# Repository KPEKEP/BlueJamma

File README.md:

# Arcade Bluetooth Controller Adapter "BlueJamma"

## Overview
This project provides a hardware and software solution to add Bluetooth gamepad support to Jamma/Chamma arcade boards (like Pandora Box), while maintaining the original physical controls functionality. The adapter allows connecting up to 2 Bluetooth gamepads simultaneously with the existing control panel.

The device is built around the ESP32-C3 SuperMini development board, which provides an excellent balance of size, features, and cost. The control program is based on the BluePad32 library and can be found in the `sketch` folder of this repository.

## Features
- Supports up to 2 Bluetooth gamepads simultaneously
- Maintains original control panel functionality
- Compatible with Jamma/Chamma arcade boards
- Easy installation and setup
- Open-source hardware and software

## Hardware
The project uses the ESP32-C3 SuperMini form factor for its compact size and built-in USB capabilities. A complete list of required components and materials can be found in the interactive [Bill of Materials](bom/ibom.html).

The PCB design incorporates elements from the [JammaKludge project](https://github.com/estechnical/jammakludge) by estechnical, which provided valuable reference for the Jamma connector implementation.

## PCB Design

## Enclosure Design
Check out the 3D render of the enclosure design:
https://github.com/KPEKEP/BlueJamma/raw/main/enclosure/export/rc3/rc3_v1.avi

STEP files for the enclosure are available in the [enclosure/export/rc3/](enclosure/export/rc3/) folder.

## Assembled Device

Assembled device: https://github.com/KPEKEP/BlueJamma/raw/main/images/assembled.MOV

Watch a demo of the device working with Bluetooth controllers:
https://github.com/KPEKEP/BlueJamma/raw/main/images/demo.mp4

## Risk Disclaimer
### ATTENTION: The device was tested only with Pandora Box, which is a Chamma board. Jamma boards are not tested yet.
### Chamma and Jamma compatibility
### IMPORTANT: The additional kicker harnesses are not supported yet.

BlueJamma was designed to be a pass-through between the arcade board and physical controls or whatever is connected next. When no input is coming from gamepads, regardless of their connection status, the system behaves as it would be a straight connection between the arcade board and physical controllers.
If an arcade board has Chamma (6-button), or regular Jamma (3-button) interface, it should work.
Please refer to the image of the layout below (side by side of top and bottom side of the PCB) and pay attention to the traces between 25,26,27,C,D,E on the right side of the PCB.

**USE AT YOUR OWN RISK**: The hardware and software in this project are provided "as is", without warranty of any kind, express or implied. The creators and contributors of this project accept no responsibility or liability for any damage, injury, or loss resulting from the use of this project's hardware, software, or documentation.

- We are not responsible for any damage to your arcade board, control panel, or other equipment
- Modify your hardware at your own risk
- Always verify connections and power requirements before use

### Components Attribution
This project uses:
- Open-source libraries and components, all properly credited in the source code
- Originally written code and hardware designs
- Third-party libraries used under their respective licenses (see Dependencies section)

### Non-Commercial Use License
This project is released under a Non-Commercial Use License. You are free to:
- Use this project for personal, non-commercial purposes
- Modify and adapt the code for personal use
- Share the project with others, provided you maintain the same license

You may NOT:
- Use this project for commercial purposes
- Sell products based on this project
- Include this project in commercial applications

## TODO
- [ ] Add kicker harness support
- [ ] Add a shadow-line for the top and bottom parts of the enclosure
- [ ] Test with Jamma board and different harness combinations
- [ ] Test video signal quality with\without BlueJamma. Some decoupling circuitry might be need.
      
## Authors and Acknowledgment
Pavel Nakaznenko, 2025

This project relies on and gratefully acknowledges the following tools and projects:

- [BluePad32](https://github.com/ricardoquesada/bluepad32) - The excellent Bluetooth gamepad support library that powers the controller functionality
- [ESP32-C3](https://www.espressif.com/en/products/socs/esp32-c3) - The RISC-V based microcontroller from Espressif
- [Arduino IDE](https://www.arduino.cc/en/software) - The development environment used for programming
- [KiCad](https://www.kicad.org/) - The open-source software used for electronic design
- [JLCPCB](https://jlcpcb.com/) - PCB manufacturing and assembly services
- [JammaKludge](https://github.com/estechnical/jammakludge) - Reference materials for Jamma connector implementation

Special thanks to all the open-source contributors and communities behind these projects.

---

Remember: This project is for non-commercial use only. All modifications and usage are at your own risk. 

LICENSE: [CC BY-NC-SA 4.0](https://creativecommons.org/licenses/by-nc-sa/4.0/)

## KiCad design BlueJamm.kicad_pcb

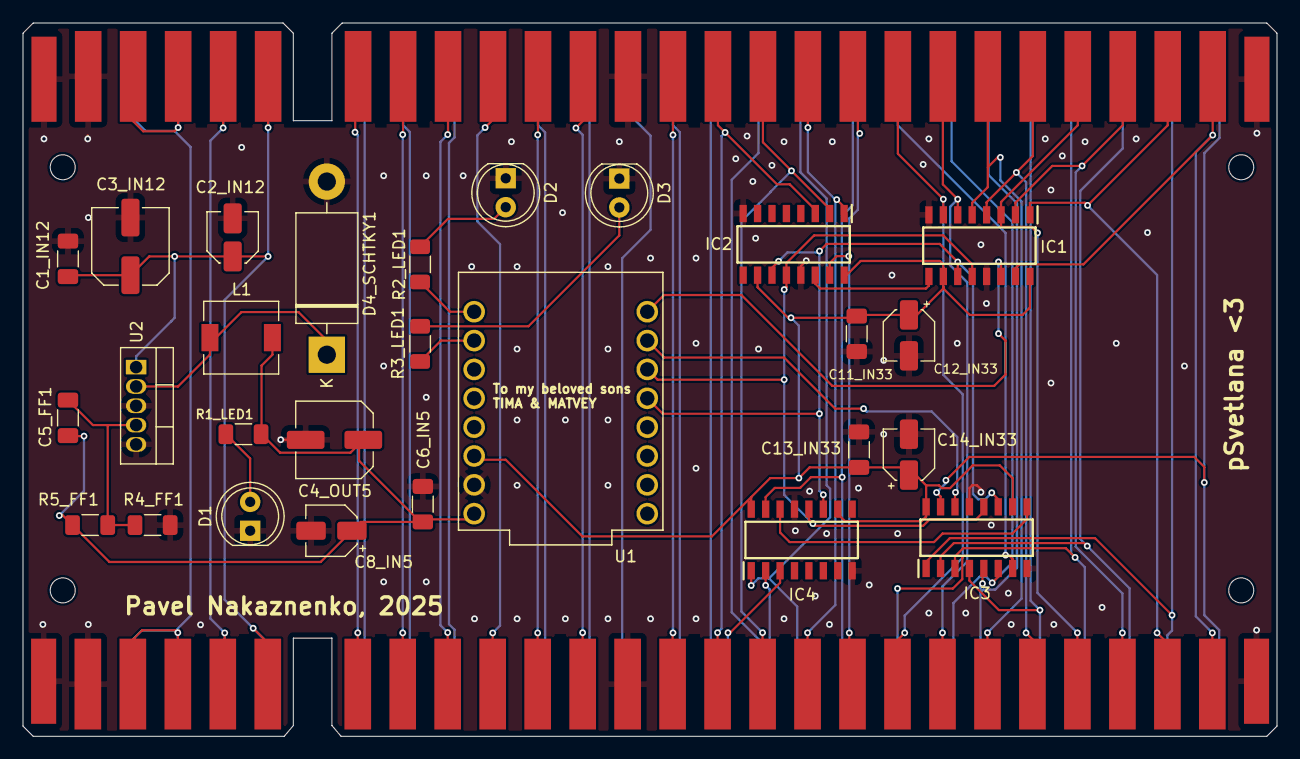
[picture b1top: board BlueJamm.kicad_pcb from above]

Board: 2 copper layers, 110.4 x 62.8 mm, 33 parts (0 on the bottom side), 57 nets.

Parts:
C1_IN12, C6_IN5, C11_IN33, C13_IN33: 0.1u; C_1206_3216Metric_Pad1.33x1.80mm_HandSolder
C2_IN12: 10u; C_Elec_4x5.4
C3_IN12: 100u; C_Elec_6.3x5.4
C4_OUT5: 220u; C_Elec_6.3x7.7
C5_FF1: 10n; C_1206_3216Metric_Pad1.33x1.80mm_HandSolder
C8_IN5, C12_IN33, C14_IN33: 10u; CP_Elec_4x5.4
Conn1: jamma; JAMMA-56
Conn2: jamma; JAMMA-56_inverted
D1, D2, D3: LED_5mm; LED_D5.0mm
D4_SCHTKY1: 1n5822; D_DO-201AD_P15.24mm_Horizontal
H1, H2, H3, H4: MountingHole_2.2mm_M2
IC1, IC2, IC3, IC4: 74HC595D; SOIC127P600X175-16N
L1: 47u; L_6.3x6.3_H3
R1_LED1: 200; R_1206_3216Metric_Pad1.30x1.75mm_HandSolder
R2_LED1, R3_LED1: 100; R_1206_3216Metric_Pad1.30x1.75mm_HandSolder
R4_FF1: 1k; R_1206_3216Metric_Pad1.30x1.75mm_HandSolder
R5_FF1: 3k; R_1206_3216Metric_Pad1.30x1.75mm_HandSolder
U1: ESP32-C3_SUPERMINI; MODULE_ESP32-C3_SUPERMINI
U2: LM2596T-ADJ; TO-220-5_Vertical_Pavel

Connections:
/3.3V: C11_IN33.1, C12_IN33.1, C13_IN33.1, C14_IN33.1, IC1.10 (~MR), IC1.16 (VCC), IC2.10 (~MR), IC2.16 (VCC), IC3.10 (~MR), IC3.16 (VCC), IC4.10 (~MR), IC4.16 (VCC), U1.3.3 (3V3)
/5V: C4_OUT5.1, C5_FF1.2, C6_IN5.1, C8_IN5.1, L1.2, R1_LED1.1, R5_FF1.1, U1.5V
/+5V_BYPASS: Conn1.3 (+5v), Conn1.4 (+5v), Conn1.C (+5v), Conn1.D (+5v), Conn2.3 (+5v), Conn2.4 (+5v), Conn2.C (+5v), Conn2.D (+5v)
/+12V_BYPASS: C1_IN12.1, C2_IN12.1, C3_IN12.1, Conn1.6 (+12v), Conn1.F (+12v), Conn2.6 (+12v), Conn2.F (+12v), U2.1 (VIN)
/-5V_BYPASS: Conn1.5 (-5v), Conn1.E (-5v), Conn2.5 (-5v), Conn2.E (-5v)
/Audio_+: Conn1.11 (Audio_+), Conn2.11 (Audio_+)
/Coin_1: Conn1.16 (Coin_1), Conn2.16 (Coin_1), IC2.3 (Q3)
/Coin_2: Conn1.T (Coin2), Conn2.T (Coin2), IC4.3 (Q3)
/Lockout_1: Conn1.9 (Lockout_1), Conn2.9 (Lockout_1)
/Lockout_2: Conn1.K (Lockout_2), Conn2.K (Lockout_2)
/Meter_1: Conn1.8 (Meter_1), Conn2.8 (Meter_1)
/Meter_2: Conn1.J (Meter_2), Conn2.J (Meter_2)
/P1_button1: Conn1.22 (P1_button1), Conn2.22 (P1_button1), IC1.5 (Q5)
/P1_button2: Conn1.23 (P1_button2), Conn2.23 (P1_button2), IC1.4 (Q4)
/P1_button3: Conn1.24 (P1_button3), Conn2.24 (P1_button3), IC1.3 (Q3)
/P1_button4: Conn1.25 (P1_button4), Conn2.25 (P1_button4), IC1.2 (Q2)
/P1_button5: Conn1.26 (P1_button5), Conn2.26 (P1_button5), IC1.1 (Q1)
/P1_button6: Conn1.27 (P1_button6), Conn2.27 (P1_button6), IC1.15 (Q0)
/P1_connected: R2_LED1.1, U1.0 (GPIO0)
/P1_down: Conn1.19 (P1_down), Conn2.19 (P1_down), IC2.15 (Q0)
/P1_left: Conn1.20 (P1_left), Conn2.20 (P1_left), IC1.7 (Q7)
/P1_right: Conn1.21 (P1_right), Conn2.21 (P1_right), IC1.6 (Q6)
/P1_start: Conn1.17 (P1_start), Conn2.17 (P1_start), IC2.2 (Q2)
/P1_up: Conn1.18 (P1_up), Conn2.18 (P1_up), IC2.1 (Q1)
/P2_button1: Conn1.Z (P2_button1), Conn2.Z (P2_button1), IC3.5 (Q5)
/P2_button2: Conn1.a (P2_button2), Conn2.a (P2_button2), IC3.4 (Q4)
/P2_button3: Conn1.b (P2_button3), Conn2.b (P2_button3), IC3.3 (Q3)
/P2_button4: Conn1.c (P2_button4), Conn2.c (P2_button4), IC3.2 (Q2)
/P2_button5: Conn1.d (P2_button5), Conn2.d (P2_button5), IC3.1 (Q1)
/P2_button6: Conn1.e (P2_button6), Conn2.e (P2_button6), IC3.15 (Q0)
/P2_connected: R3_LED1.1, U1.1 (GPIO1)
/P2_down: Conn1.W (P2_down), Conn2.W (P2_down), IC4.15 (Q0)
/P2_left: Conn1.X (P2_left), Conn2.X (P2_left), IC3.7 (Q7)
/P2_right: Conn1.Y (P2_right), Conn2.Y (P2_right), IC3.6 (Q6)
/P2_start: Conn1.U (P2_start), Conn2.U (P2_start), IC4.2 (Q2)
/P2_up: Conn1.V (P2_up), Conn2.V (P2_up), IC4.1 (Q1)
/RCLK: IC1.12 (STCP), IC2.12 (STCP), IC3.12 (STCP), IC4.12 (STCP), U1.10 (GPIO10)
/SER_P1: IC1.14 (DS), U1.21 (GPIO21)
/SER_P2: IC3.14 (DS), U1.20 (GPIO20)
/SRCLK: IC1.11 (SHCP), IC2.11 (SHCP), IC3.11 (SHCP), IC4.11 (SHCP), U1.9 (GPIO9)
/Service_switch: Conn1.R (Service_switch), Conn2.R (Service_switch)
/Speaker_+: Conn1.10 (Speaker_+), Conn2.10 (Speaker_+)
/Speaker_-: Conn1.L (Speaker_-), Conn2.L (Speaker_-)
/Test_switch: Conn1.15 (Test_switch), Conn2.15 (Test_switch)
/Tilt_switch: Conn1.S (Tilt_switch), Conn2.S (Tilt_switch)
/VidBlue: Conn1.13 (Video_blue), Conn2.13 (Video_blue)
/VidGreen: Conn1.N (Video_green), Conn2.N (Video_green)
/VidRed: Conn1.12 (Video_red), Conn2.12 (Video_red)
/VidSync: Conn1.P (Video_sync), Conn2.P (Video_sync)
GND: C1_IN12.2, C2_IN12.2, C3_IN12.2, C4_OUT5.2, C6_IN5.2, C8_IN5.2, C11_IN33.2, C12_IN33.2, C13_IN33.2, C14_IN33.2, Conn1.1 (Gnd), Conn1.2 (Gnd), Conn1.14 (Video_gnd), Conn1.28 (Gnd), Conn1.A (Gnd), Conn1.B (Gnd), Conn1.M (Audio_gnd), Conn1.f (Gnd), Conn2.1 (Gnd), Conn2.2 (Gnd), Conn2.14 (Video_gnd), Conn2.28 (Gnd), Conn2.A (Gnd), Conn2.B (Gnd), Conn2.M (Audio_gnd), Conn2.f (Gnd), D1.1, D2.1, D3.1, D4_SCHTKY1.2 (A), IC1.8 (GND), IC1.13 (~OE), IC2.8 (GND), IC2.13 (~OE), IC3.8 (GND), IC3.13 (~OE), IC4.8 (GND), IC4.13 (~OE), R4_FF1.1, U1.G (GND), U2.3 (GND), U2.5 (~ON/OFF)
unnamed: D1.2, R1_LED1.2
unnamed: D2.2, R2_LED1.2
unnamed: D3.2, R3_LED1.2
unnamed: D4_SCHTKY1.1 (K), L1.1, U2.2 (OUT)
unnamed: IC1.9 (Q7S), IC2.14 (DS)
unnamed: IC3.9 (Q7S), IC4.14 (DS)
unnamed: C5_FF1.1, R4_FF1.2, R5_FF1.2, U2.4 (FB)

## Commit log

2025-01-27 missing resources
2025-01-27 improved enclosure, readme update
2025-01-27 Jamma and Chamma clarification, pcb layout image
2025-01-27 kick harness are not supported yet
2025-01-27 updated todo
2025-01-27 better wording in readme
